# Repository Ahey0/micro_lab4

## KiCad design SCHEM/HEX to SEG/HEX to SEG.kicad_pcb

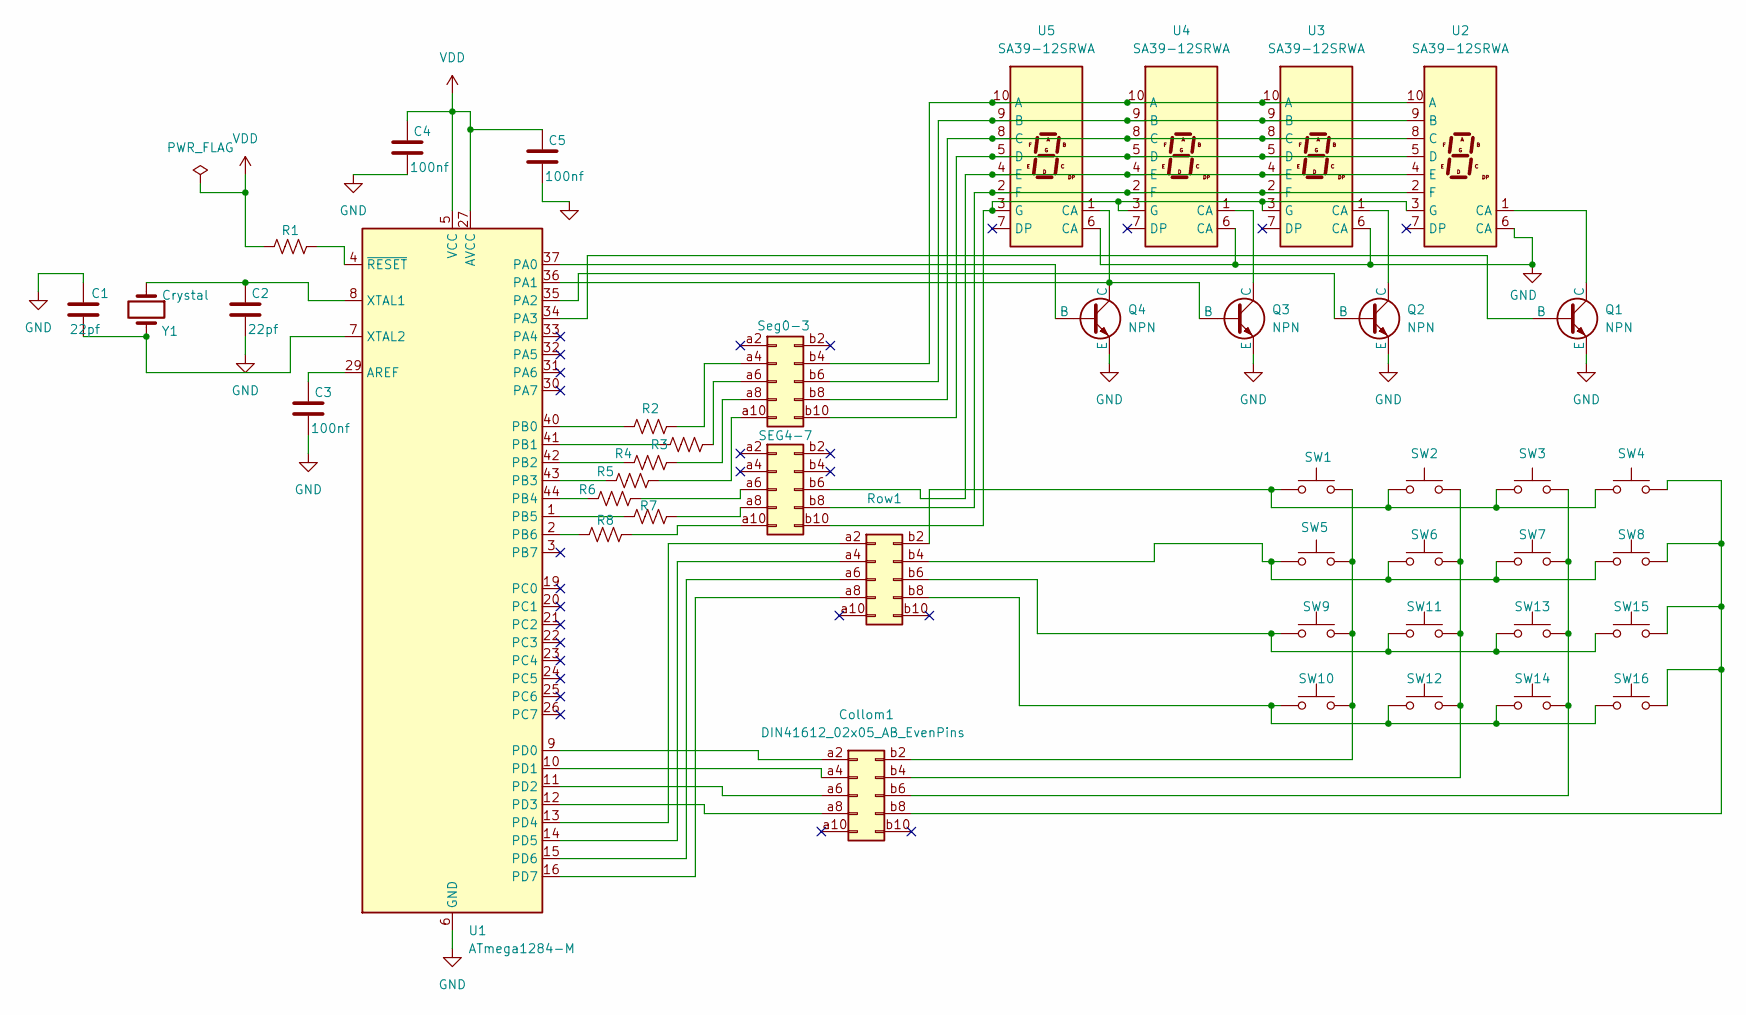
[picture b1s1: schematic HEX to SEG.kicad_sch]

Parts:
C1, C2: 22pf; C_0201_0603Metric
C3, C4, C5: 100nf; C_0201_0603Metric
Collom1: DIN41612_02x05_AB_EvenPins; DIN41612_B3_2x5_Female_Vertical_THT
Q1, Q2, Q3, Q4: NPN; TO-92_HandSolder
R1: 10k; R_0402_1005Metric
R2, R3, R4, R5, R6, R7, R8: R_US; R_Axial_Power_L20.0mm_W6.4mm_P30.48mm
Row1: DIN41612_02x05_AB_EvenPins; DIN41612_B3_2x5_Female_Vertical_THT
SEG4-7: DIN41612_02x05_AB_EvenPins; DIN41612_B3_2x5_Female_Vertical_THT
SW1, SW2, SW3, SW4, SW5, SW6, SW7, SW8, SW9, SW10, SW11, SW12, SW13, SW14, SW15, SW16: SW_Push; SW_PUSH_6mm_H4.3mm
Seg0-3: DIN41612_02x05_AB_EvenPins; DIN41612_B3_2x5_Female_Vertical_THT
U1: ATmega1284-M; QFN-44-1EP_7x7mm_P0.5mm_EP5.2x5.2mm
U2, U3, U4, U5: SA39-12SRWA; D1X8K
Y1: Crystal; Crystal_SMD_EuroQuartz_EQ161-2Pin_3.2x1.5mm

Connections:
GND: C1.1, C2.2, C3.2, C4.2, C5.2, Q1.3 (E), Q2.3 (E), Q3.3 (E), Q4.3 (E), U1.6 (GND), U1.18 (GND), U1.28 (GND), U1.39 (GND), U1.45 (GND), U2.6 (CA), U3.6 (CA), U4.6 (CA), U5.6 (CA)
unnamed: Collom1.a2, U1.9 (PD0)
unnamed: Collom1.a4, U1.10 (PD1)
unnamed: Collom1.a6, U1.11 (PD2)
unnamed: Collom1.a8, U1.12 (PD3)
unnamed: Collom1.b2, SW1.2, SW5.2, SW9.2, SW10.2
unnamed: Collom1.b4, SW2.2, SW6.2, SW11.2, SW12.2
unnamed: Collom1.b6, SW3.2, SW7.2, SW13.2, SW14.2
unnamed: Collom1.b8, SW4.2, SW8.2, SW15.2, SW16.2
unnamed: Q1.2 (B), U1.34 (PA3)
unnamed: Q1.1 (C), U2.1 (CA)
unnamed: Q2.2 (B), U1.35 (PA2)
unnamed: Q2.1 (C), U3.1 (CA)
unnamed: Q3.2 (B), Q4.1 (C), U1.36 (PA1), U5.1 (CA)
unnamed: Q3.1 (C), U4.1 (CA)
unnamed: Q4.2 (B), U1.37 (PA0)
unnamed: Row1.a2, U1.13 (PD4)
unnamed: Row1.a4, U1.14 (PD5)
unnamed: Row1.a6, U1.15 (PD6)
unnamed: Row1.a8, U1.16 (PD7)
unnamed: Row1.b2, SW1.1, SW2.1, SW3.1, SW4.1
unnamed: Row1.b4, SW5.1, SW6.1, SW7.1, SW8.1
unnamed: Row1.b6, SW9.1, SW11.1, SW13.1, SW15.1
unnamed: Row1.b8, SW10.1, SW12.1, SW14.1, SW16.1
unnamed: R6.2, SEG4-7.a6
unnamed: R7.2, SEG4-7.a8
unnamed: R8.2, SEG4-7.a10
unnamed: SEG4-7.b6, U2.4 (E), U3.4 (E), U4.4 (E), U5.4 (E)
unnamed: SEG4-7.b8, U2.2 (F), U3.2 (F), U4.2 (F), U5.2 (F)
unnamed: SEG4-7.b10, U2.3 (G), U3.3 (G), U4.3 (G), U5.3 (G)
unnamed: R2.2, Seg0-3.a4
unnamed: R3.2, Seg0-3.a6
unnamed: R4.2, Seg0-3.a8
unnamed: R5.2, Seg0-3.a10
unnamed: Seg0-3.b4, U2.10 (A), U3.10 (A), U4.10 (A), U5.10 (A)
unnamed: Seg0-3.b6, U2.9 (B), U3.9 (B), U4.9 (B), U5.9 (B)
unnamed: Seg0-3.b8, U2.8 (C), U3.8 (C), U4.8 (C), U5.8 (C)
unnamed: Seg0-3.b10, U2.5 (D), U3.5 (D), U4.5 (D), U5.5 (D)
unnamed: C3.1, U1.29 (AREF)
unnamed: R2.1, U1.40 (PB0)
unnamed: R3.1, U1.41 (PB1)
unnamed: R4.1, U1.42 (PB2)
unnamed: R5.1, U1.43 (PB3)
unnamed: R6.1, U1.44 (PB4)
unnamed: R7.1, U1.1 (PB5)
unnamed: R8.1, U1.2 (PB6)
unnamed: C2.1, U1.8 (XTAL1), Y1.1
unnamed: C1.2, U1.7 (XTAL2), Y1.2
unnamed: R1.2, U1.4 (~RESET)
VDD: C4.1, C5.1, R1.1, U1.5 (VCC), U1.17 (VCC), U1.27 (AVCC), U1.38 (VCC)

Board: 2 copper layers, 43 parts (0 on the bottom side), 50 nets, no tracks yet.

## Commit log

2025-04-16 Initial codes
2025-05-04 Code Fied | NO PCB
